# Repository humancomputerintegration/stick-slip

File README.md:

# Stick&Slip

This is a repository for the prototype Stick&Slip device created by Alex Mazursky, Jacob Serfaty, and Pedro Lopes at the University of Chicago's [Human Computer Integration Lab](https://lab.plopes.org/). Stick&Slip is a wearable approach to alter the friction of everyday objects using liquid coatings on the fingerpad!

## Repository Structure

* `Arduino` contains code for the microcontroller (ESP32).
* `PCB` contains the KICAD files for our custom PCB.
* `3D-prints` contains models for the wearable droplet generator and bracelet (.stl files). These can be printed with most SLA printers.

## Hardware

To reproduce our experience, we include the KiCad files to manufacture our delivery mechanism. In addition to the PCB and included SMT components, the device uses a Seeeduino Xiao ESP32C3 and two mini peristaltic pumps (Takasago Fluidic Systems, RP-Q) connected to thin silicone tubing (ID = 1 mm; OD = 2 mm) via barbed connectors. Each tube is then connected to the droplet generator.

## Citing

When using or building upon this device in an academic publication, please consider citing as follows:

Alex Mazursky, Jacob Serfaty, and Pedro Lopes. 2024. Stick&Slip: Altering Fingerpad Friction via Liquid Coatings. In Proceedings of the CHI Conference on Human Factors in Computing Systems (CHI ’24), May 11–16, 2024, Honolulu, HI, USA. ACM, New York, NY, USA, 14 pages. https://doi.org/10.1145/3613904.3642299

## Contact

For any questions about this repository, please contact alexmazursky@uchicago.edu

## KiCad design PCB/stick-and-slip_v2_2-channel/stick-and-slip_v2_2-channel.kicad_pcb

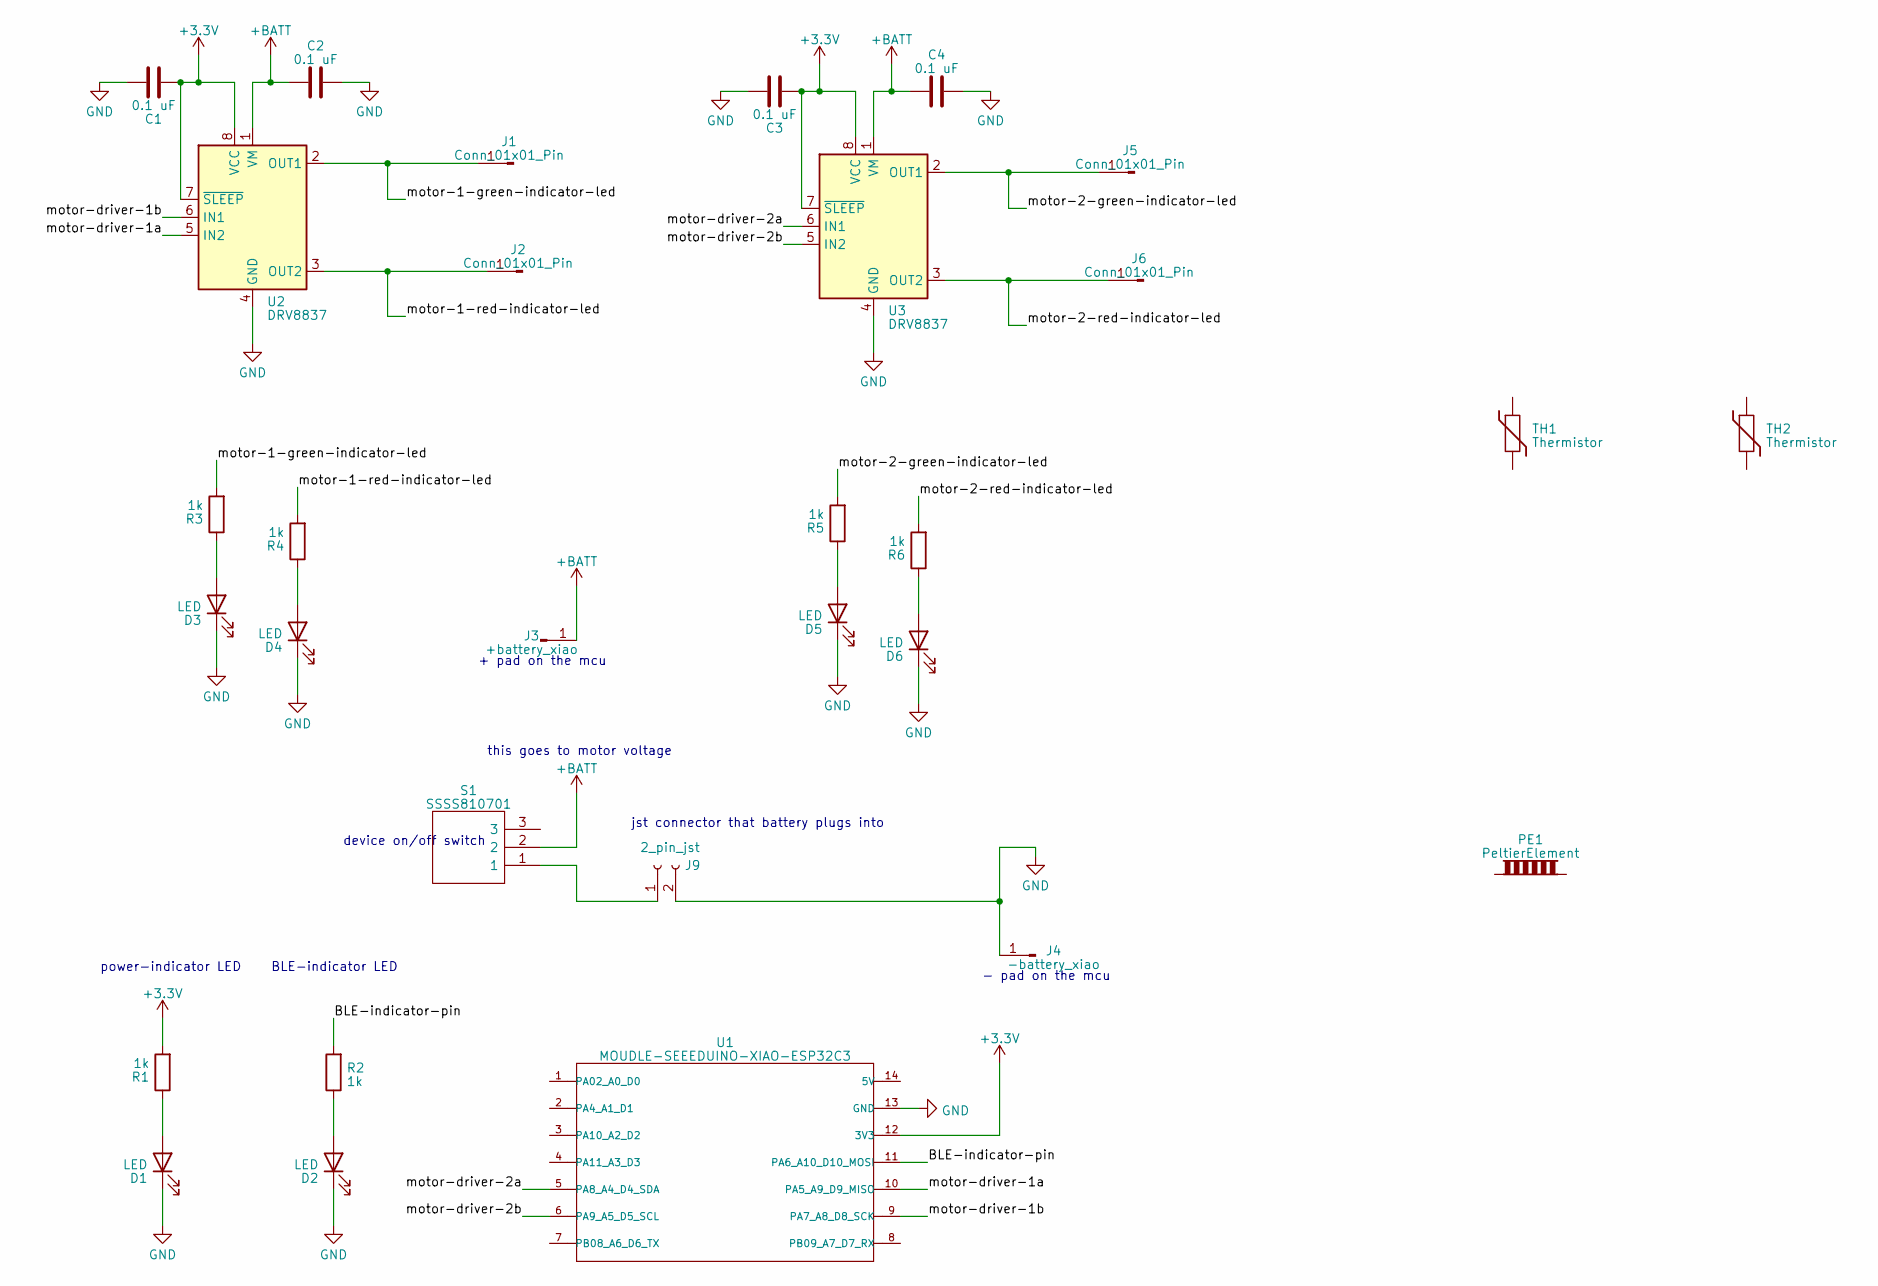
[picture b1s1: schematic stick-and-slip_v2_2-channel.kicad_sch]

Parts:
C1, C2, C3, C4: 0.1 uF; C_0603_1608Metric
D1, D2, D3, D4, D5, D6: LED; LED_0603_1608Metric
J1, J2, J5, J6: Conn_01x01_Pin; TestPoint_Loop_D1.80mm_Drill1.0mm_Beaded
J3: +battery_xiao; TestPoint_Pad_1.0x1.0mm
J4: -battery_xiao; TestPoint_Pad_1.0x1.0mm
J9: 2_pin_jst; JST_PH_S2B-PH-K_1x02_P2.00mm_Horizontal
PE1: PeltierElement
R1, R2, R3, R4, R5, R6: 1k; R_0603_1608Metric
S1: SSSS810701; Manufacturer_Part_Number SSSS810701; Mouser Part Number 688-SSSS810701
TH1, TH2: Thermistor
U1: MOUDLE-SEEEDUINO-XIAO-ESP32C3; MOUDLE14P-SMD-2.54-21X17.8MM
U2, U3: DRV8837; WSON-8-1EP_2x2mm_P0.5mm_EP0.9x1.6mm

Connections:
+3.3V: C1.1, C3.1, R1.2, U1.12 (3V3), U2.7 (~SLEEP), U2.8 (VCC), U3.7 (~SLEEP), U3.8 (VCC)
+BATT: C2.1, C4.1, J3.1, S1.2, U2.1 (VM), U3.1 (VM)
/BLE-indicator-pin: R2.2, U1.11 (PA6_A10_D10_MOSI)
/motor-1-green-indicator-led: J1.1, R3.2, U2.2 (OUT1)
/motor-1-red-indicator-led: J2.1, R4.2, U2.3 (OUT2)
/motor-2-green-indicator-led: J5.1, R5.2, U3.2 (OUT1)
/motor-2-red-indicator-led: J6.1, R6.2, U3.3 (OUT2)
/motor-driver-1a: U1.10 (PA5_A9_D9_MISO), U2.5 (IN2)
/motor-driver-1b: U1.9 (PA7_A8_D8_SCK), U2.6 (IN1)
/motor-driver-2a: U1.5 (PA8_A4_D4_SDA), U3.6 (IN1)
/motor-driver-2b: U1.6 (PA9_A5_D5_SCL), U3.5 (IN2)
GND: C1.2, C2.2, C3.2, C4.2, D1.1 (K), D2.1 (K), D3.1 (K), D4.1 (K), D5.1 (K), D6.1 (K), J4.1, J9.2, U1.13 (GND), U2.4 (GND), U2.9 (GND), U3.4 (GND), U3.9 (GND)
unnamed: D1.2 (A), R1.1
unnamed: D2.2 (A), R2.1
unnamed: D3.2 (A), R3.1
unnamed: D4.2 (A), R4.1
unnamed: D5.2 (A), R5.1
unnamed: D6.2 (A), R6.1
unnamed: J9.1, S1.1

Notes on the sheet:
- pad on the mcu
device on/off switch
this goes to motor voltage
BLE-indicator LED
power-indicator LED
jst connector that battery plugs into
+ pad on the mcu

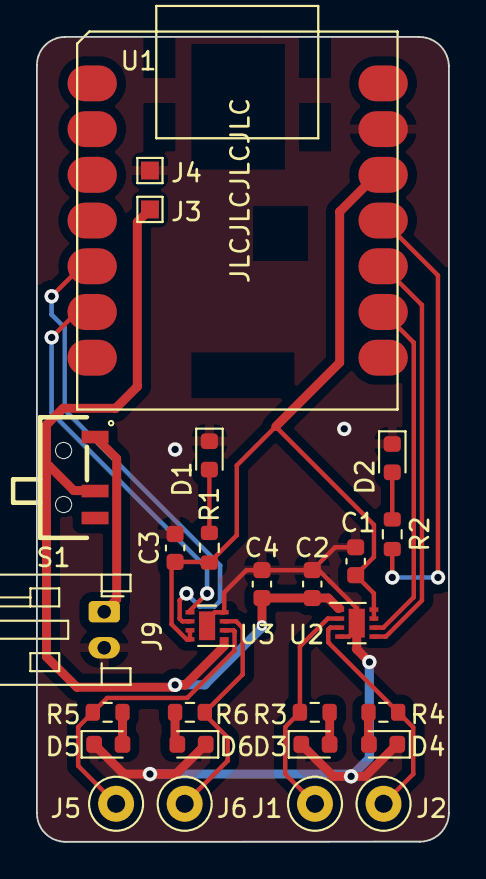
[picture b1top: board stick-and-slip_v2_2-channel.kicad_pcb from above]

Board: 2 copper layers, 22.9 x 44.7 mm, 27 parts (0 on the bottom side), 19 nets.

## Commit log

2022-07-19 first
2024-05-06 cleaning repo
2024-05-06 Code for the ESP32 XIAO.
2024-05-06 Populating folders with code, cad, and images.
2024-05-07 Cleaning folder to V2 only.
